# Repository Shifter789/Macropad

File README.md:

# Macropad
A simple macropad that has a oled display.

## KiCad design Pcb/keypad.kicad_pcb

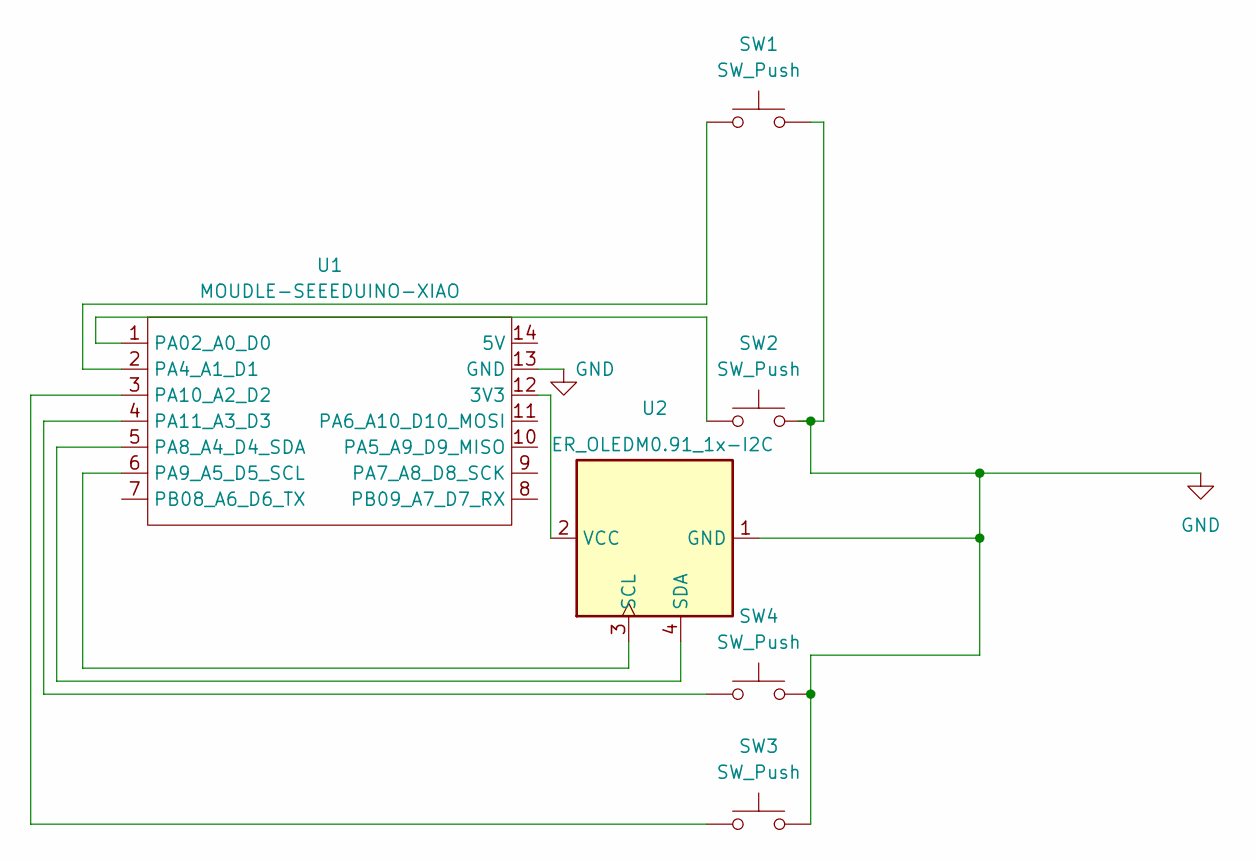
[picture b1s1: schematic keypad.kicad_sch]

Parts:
SW1, SW2, SW3, SW4: SW_Push; SW_Cherry_MX_1.00u_PCB
U1: MOUDLE-SEEEDUINO-XIAO; XIAO-Generic-Hybrid-14P-2.54-21X17.8MM
U2: ER_OLEDM0.91_1x-I2C

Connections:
GND: SW1.2, SW2.2, SW3.2, SW4.2, U1.13 (GND), U2.1 (GND)
unnamed: U1.12 (3V3), U2.2 (VCC)
unnamed: SW2.1, U1.1 (PA02_A0_D0)
unnamed: SW1.1, U1.2 (PA4_A1_D1)
unnamed: U1.5 (PA8_A4_D4_SDA), U2.4 (SDA)
unnamed: U1.6 (PA9_A5_D5_SCL), U2.3 (SCL)
unnamed: SW3.1, U1.3 (PA10_A2_D2)
unnamed: SW4.1, U1.4 (PA11_A3_D3)

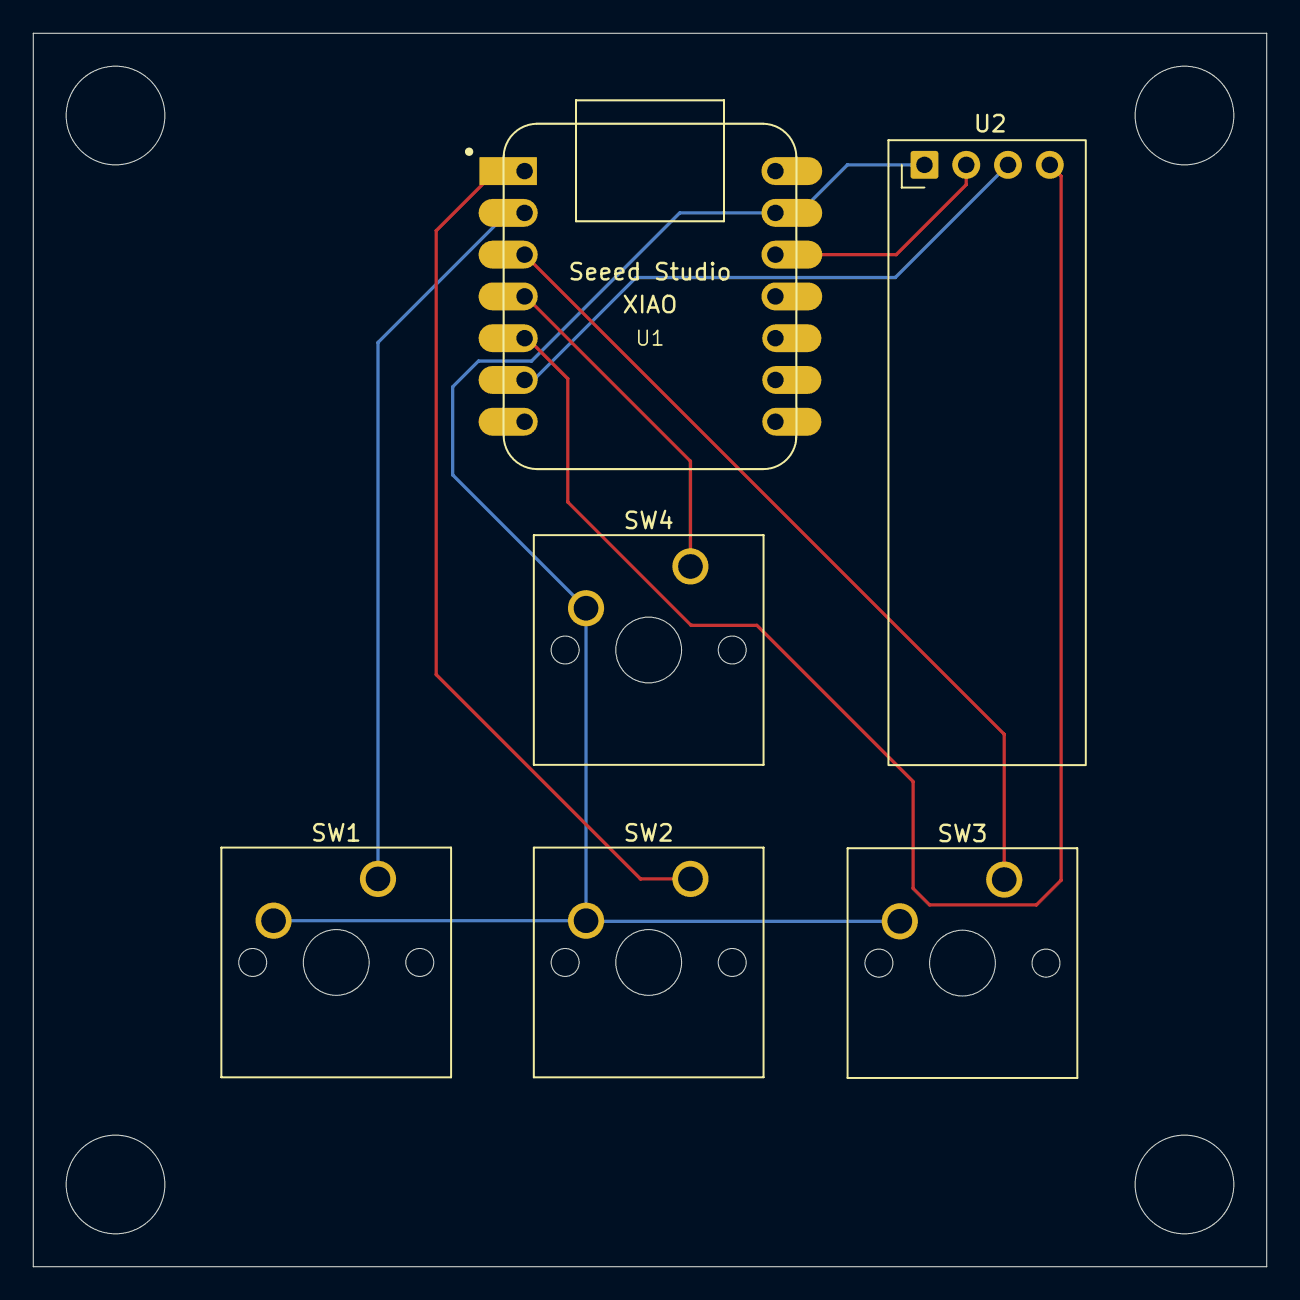
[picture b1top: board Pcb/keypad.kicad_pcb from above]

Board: 2 copper layers, 75.0 x 75.0 mm, 6 parts (0 on the bottom side), 8 nets.

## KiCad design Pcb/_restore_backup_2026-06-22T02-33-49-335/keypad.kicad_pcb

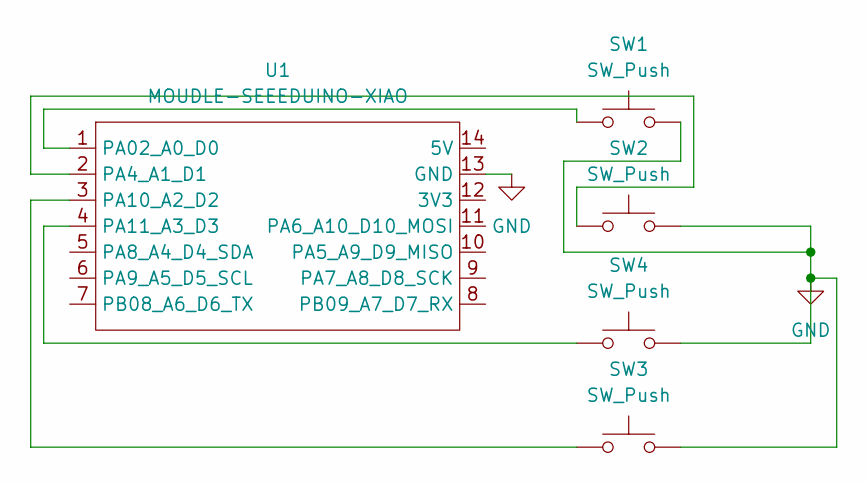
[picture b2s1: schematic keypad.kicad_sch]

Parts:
SW1, SW2, SW3, SW4: SW_Push; SW_Cherry_MX_1.00u_PCB
U1: MOUDLE-SEEEDUINO-XIAO; XIAO-Generic-Hybrid-14P-2.54-21X17.8MM

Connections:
GND: SW1.2, SW2.2, SW3.2, SW4.2, U1.13 (GND)
unnamed: SW1.1, U1.1 (PA02_A0_D0)
unnamed: SW2.1, U1.2 (PA4_A1_D1)
unnamed: SW3.1, U1.3 (PA10_A2_D2)
unnamed: SW4.1, U1.4 (PA11_A3_D3)

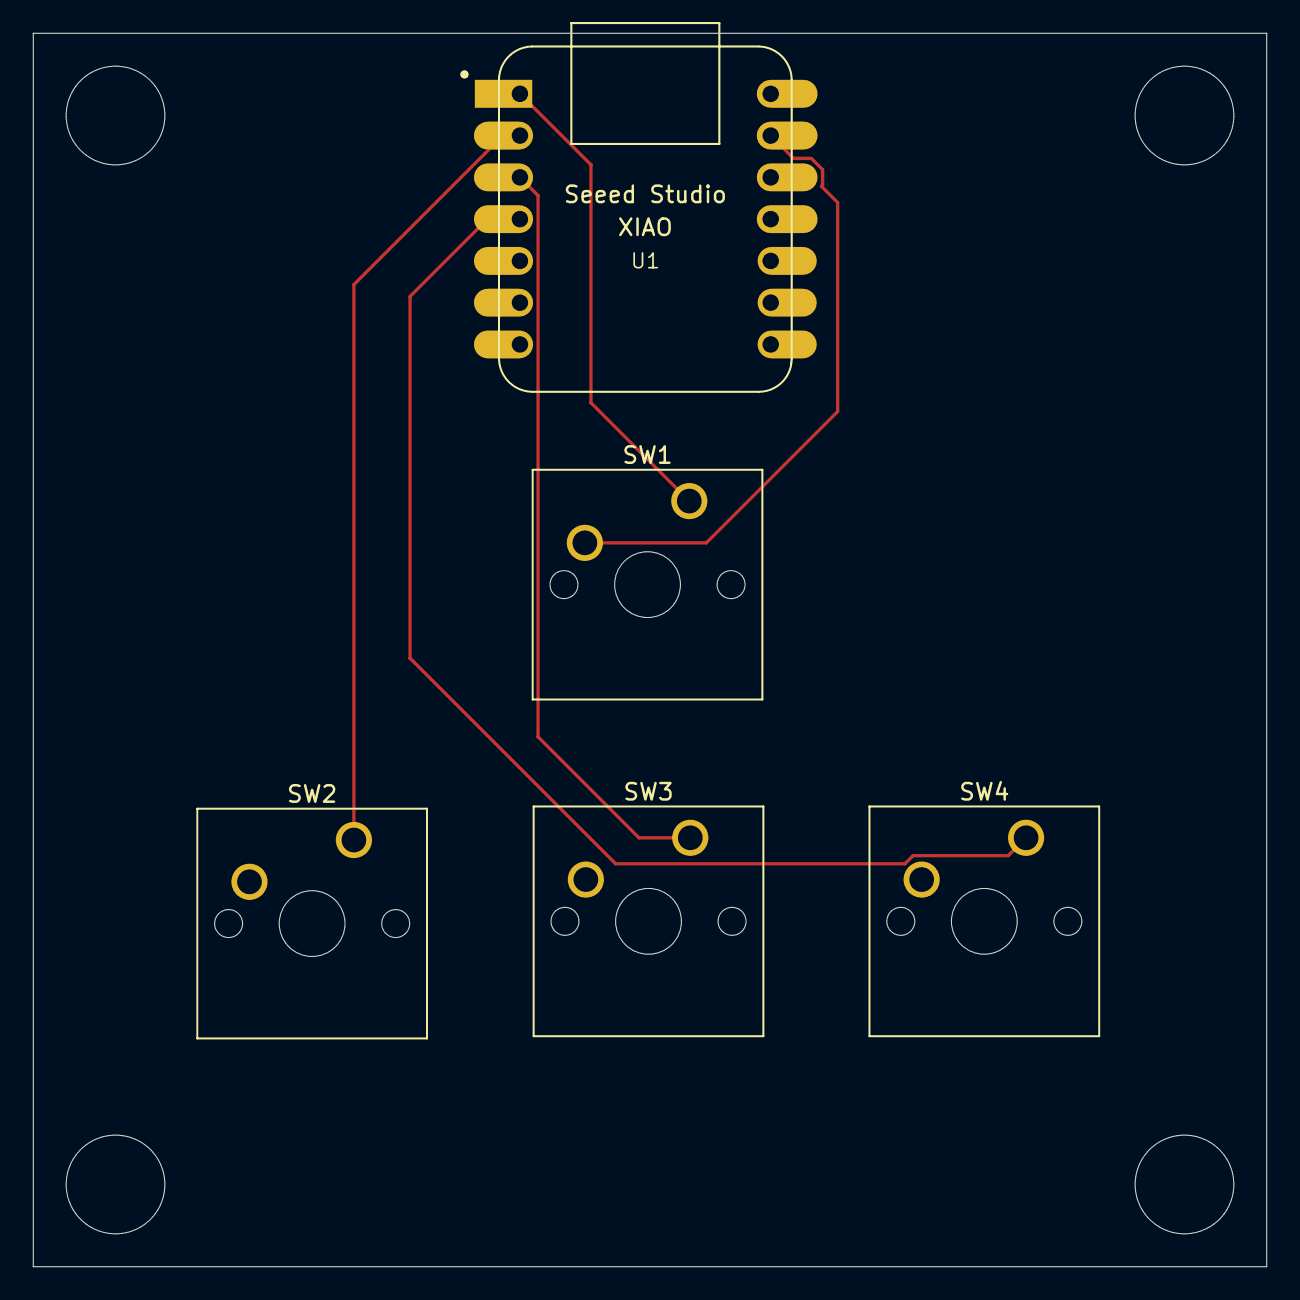
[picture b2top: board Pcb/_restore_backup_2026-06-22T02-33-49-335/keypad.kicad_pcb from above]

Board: 2 copper layers, 75.0 x 75.0 mm, 5 parts (0 on the bottom side), 5 nets.

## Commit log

2026-06-09 added pcb files and learned how to design this
2026-06-09 fixed base design
2026-06-22 worked on pcb
2026-06-22 fixed
2026-06-22 pcb design
2026-06-23 added Cad files and fixed Pcb errors
2026-06-25 pcb ch
